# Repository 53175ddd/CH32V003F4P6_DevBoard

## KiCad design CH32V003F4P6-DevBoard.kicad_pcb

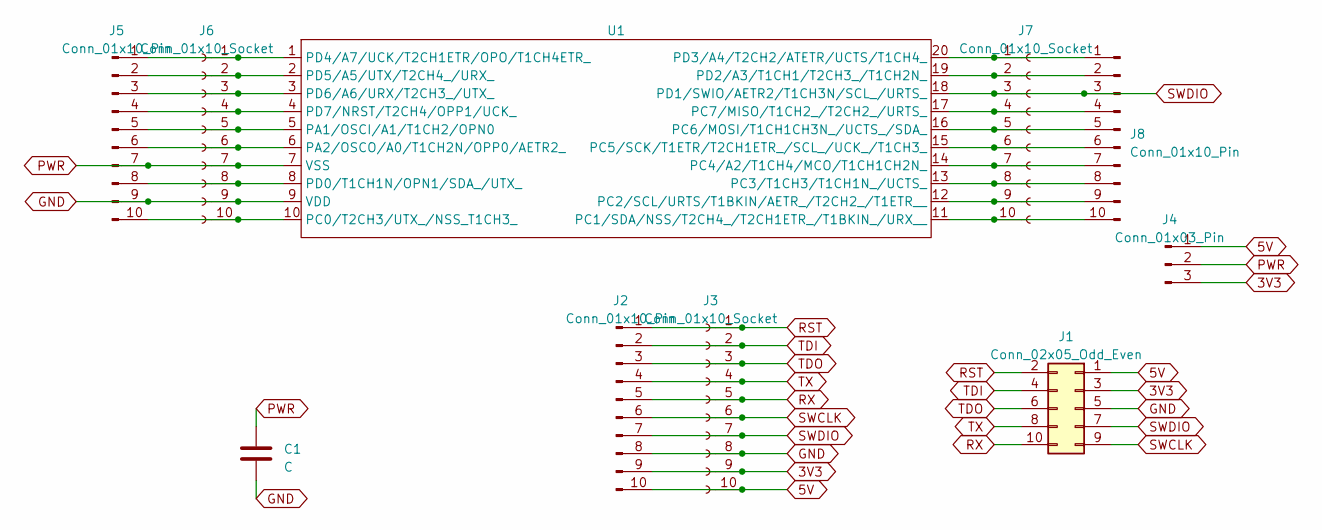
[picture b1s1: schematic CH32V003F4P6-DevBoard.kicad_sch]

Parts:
C1: C; C_0603_1608Metric
J1: Conn_02x05_Odd_Even; PinSocket_2x05_P2.54mm_Vertical
J2, J5, J8: Conn_01x10_Pin; PinHeader_1x10_P2.54mm_Vertical
J3, J6, J7: Conn_01x10_Socket; PinSocket_1x10_P2.54mm_Vertical
J4: Conn_01x03_Pin; PinHeader_1x03_P2.54mm_Vertical
U1: SSOP-20_4.4x6.5mm_P0.65mm

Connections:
3V3: J1.3, J2.9, J3.9, J4.3
5V: J1.1, J2.10, J3.10, J4.1
GND: C1.2, J1.5, J2.8, J3.8, J5.9, J6.9, U1.9 (VDD)
unnamed: J5.1, J6.1, U1.1 (PD4/A7/UCK/T2CH1ETR/OPO/T1CH4ETR_)
unnamed: J5.2, J6.2, U1.2 (PD5/A5/UTX/T2CH4_/URX_)
unnamed: J5.3, J6.3, U1.3 (PD6/A6/URX/T2CH3_/UTX_)
unnamed: J5.4, J6.4, U1.4 (PD7/NRST/T2CH4/OPP1/UCK_)
unnamed: J5.5, J6.5, U1.5 (PA1/OSCI/A1/T1CH2/OPN0)
unnamed: J5.6, J6.6, U1.6 (PA2/OSCO/A0/T1CH2N/OPP0/AETR2_)
unnamed: J5.8, J6.8, U1.8 (PD0/T1CH1N/OPN1/SDA_/UTX_)
unnamed: J5.10, J6.10, U1.10 (PC0/T2CH3/UTX_/NSS_T1CH3_)
unnamed: J7.1, J8.1, U1.20 (PD3/A4/T2CH2/ATETR/UCTS/T1CH4_)
unnamed: J7.2, J8.2, U1.19 (PD2/A3/T1CH1/T2CH3_/T1CH2N_)
unnamed: J7.4, J8.4, U1.17 (PC7/MISO/T1CH2_/T2CH2_/URTS_)
unnamed: J7.5, J8.5, U1.16 (PC6/MOSI/T1CH1CH3N_/UCTS_/SDA_)
unnamed: J7.6, J8.6, U1.15 (PC5/SCK/T1ETR/T2CH1ETR_/SCL_/UCK_/T1CH3_)
unnamed: J7.7, J8.7, U1.14 (PC4/A2/T1CH4/MCO/T1CH1CH2N_)
unnamed: J7.8, J8.8, U1.13 (PC3/T1CH3/T1CH1N_/UCTS_)
unnamed: J7.9, J8.9, U1.12 (PC2/SCL/URTS/T1BKIN/AETR_/T2CH2_/T1ETR__)
unnamed: J7.10, J8.10, U1.11 (PC1/SDA/NSS/T2CH4_/T2CH1ETR_/T1BKIN_/UR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)
PWR: C1.1, J4.2, J5.7, J6.7, U1.7 (VSS)
RST: J1.2, J2.1, J3.1
RX: J1.10, J2.5, J3.5
SWCLK: J1.9, J2.6, J3.6
SWDIO: J1.7, J2.7, J3.7, J7.3, J8.3, U1.18 (PD1/SWIO/AETR2/T1CH3N/SCL_/URTS_)
TDI: J1.4, J2.2, J3.2
TDO: J1.6, J2.3, J3.3
TX: J1.8, J2.4, J3.4

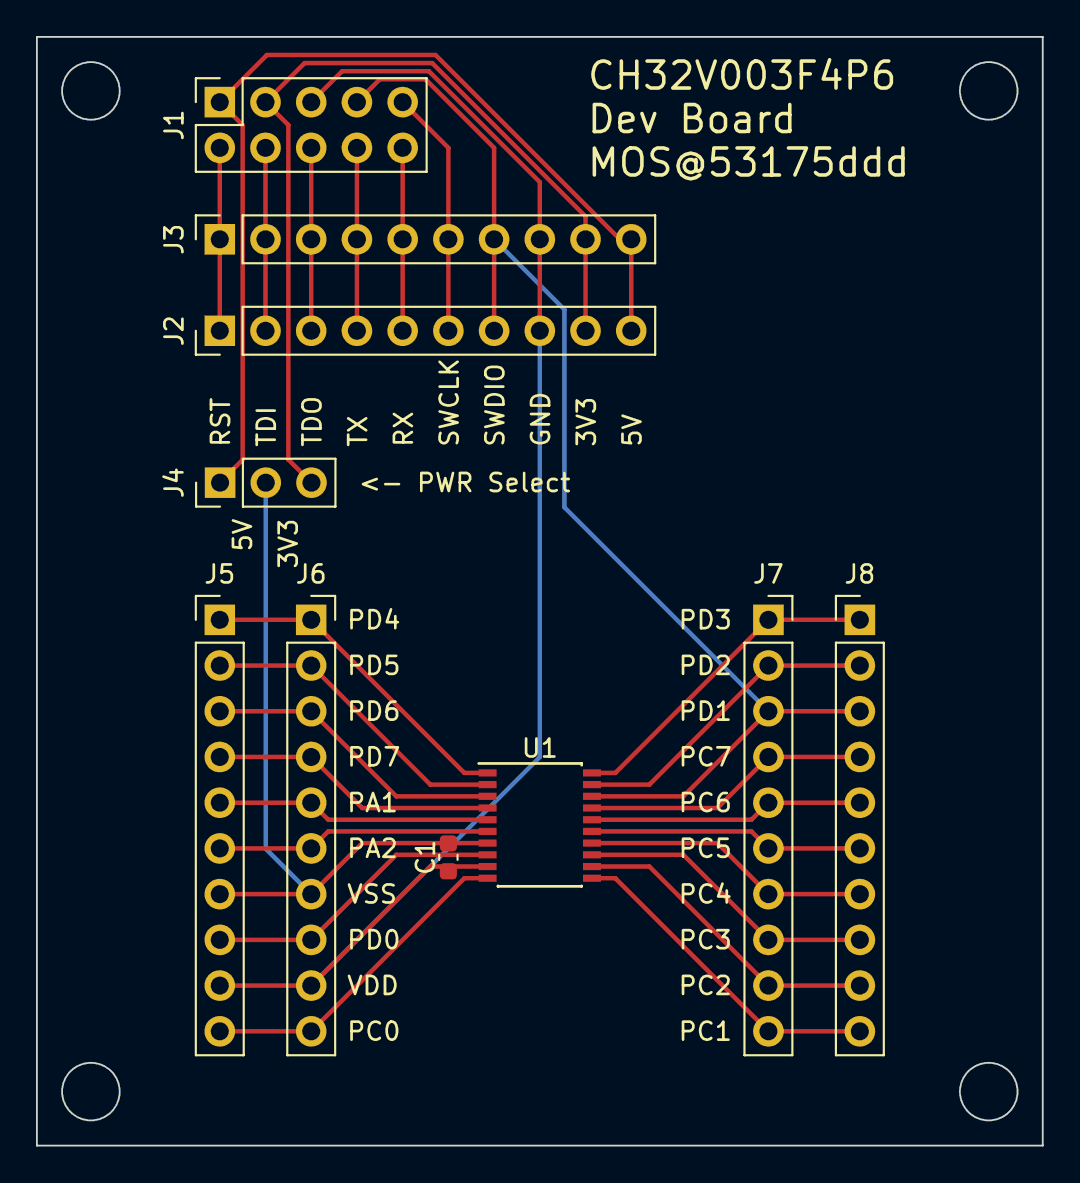
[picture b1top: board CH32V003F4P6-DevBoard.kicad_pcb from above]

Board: 2 copper layers, 55.9 x 61.6 mm, 10 parts (0 on the bottom side), 28 nets.
